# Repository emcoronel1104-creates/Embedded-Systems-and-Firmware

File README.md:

# Embedded-Systems-and-Firmware
Microcontroller projects, bare-metal firmware developments, and sensor interfacing protocols (C/C++).

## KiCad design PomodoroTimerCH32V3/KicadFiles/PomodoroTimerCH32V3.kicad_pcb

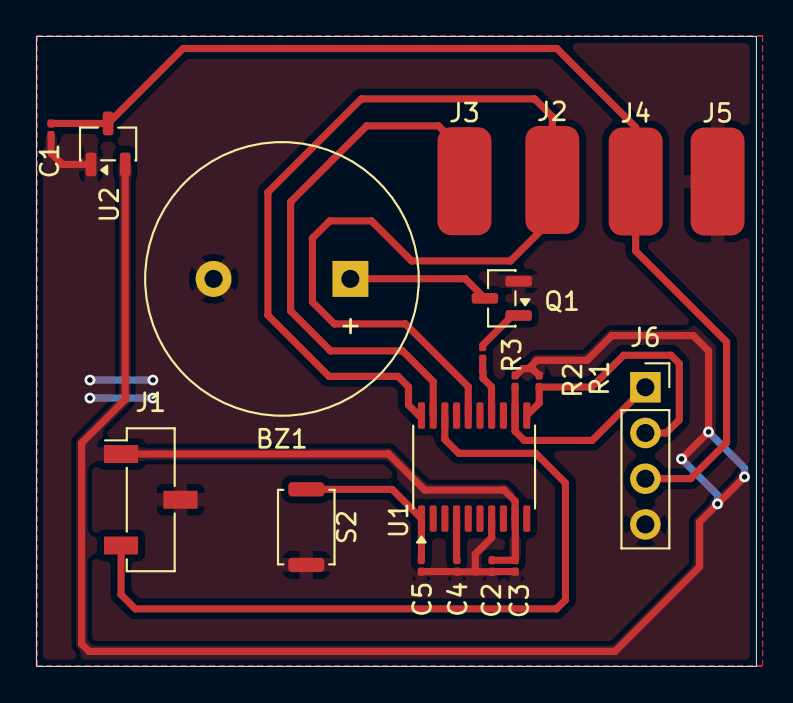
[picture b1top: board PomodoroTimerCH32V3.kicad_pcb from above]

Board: 2 copper layers, 40.0 x 35.0 mm, 19 parts (0 on the bottom side), 13 nets.

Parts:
BZ1: Buzzer; Buzzer_15x7.5RM7.6
C1, C2: 4.7uF; C_0201_0603Metric
C3, C4: 100uF; C_0201_0603Metric
C5: 0.1uF; C_0201_0603Metric
J1: Conn_01x03_Socket; PinSocket_1x03_P2.54mm_Vertical_SMD_Pin1Left
J2, J3, J4, J5: Conn_01x01_Pin; SolderWirePad_1x01_SMD_3x6mm
J6: Conn_01x02_Socket; PinSocket_1x04_P2.54mm_Vertical
Q1: BSS138; SOT-23
R1, R2, R3: 10k; R_0201_0603Metric
S2: SW_Push; SW_Push_SPST_NO_Alps_SKRK
U1: CH32V003FxPx; TSSOP-20_4.4x6.5mm_P0.65mm
U2: XC6206PxxxMR; SOT-23-3

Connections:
+3.3V: C2.1, C3.1, J1.1, R1.2, R2.2, U1.9 (VDD), U2.2 (VO)
+5V: C1.1, J4.1 (Pin_1_1), J6.3 (VCC), U2.3 (VI)
BUZZ: R3.1, U1.14 (PC4)
Button1: C5.1, S2.1, U1.1 (PD4)
GND: BZ1.2 (-), C1.2, C2.2, C3.2, C4.2, C5.2, J1.2, J5.1 (Pin_1_1), J6.4 (GND), Q1.2 (S), S2.2, U1.7 (VSS), U2.1 (GND)
NRST: C4.1, U1.4 (PD7)
unnamed: BZ1.1 (+), Q1.3 (D)
unnamed: Q1.1 (G), R3.2
PDIO: J1.3, U1.18 (PD1)
SCL: J6.1 (SCL), R2.1, U1.12 (PC2)
SDA: J6.2 (SDA), R1.1, U1.11 (PC1)
Touch1: J2.1 (Pin_1_1), U1.16 (PC6), U1.20 (PD3)
Touch2: J3.1 (Pin_1_1), U1.17 (PC7), U1.19 (PD2)

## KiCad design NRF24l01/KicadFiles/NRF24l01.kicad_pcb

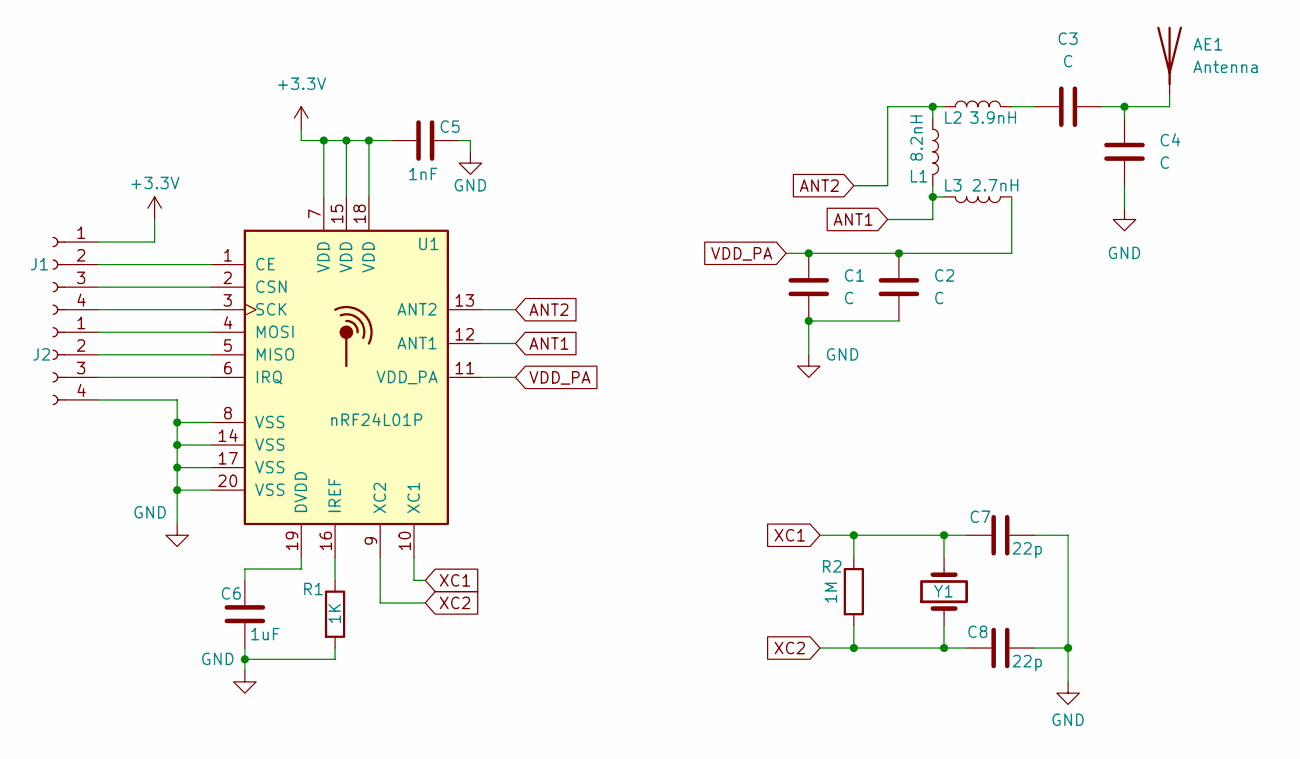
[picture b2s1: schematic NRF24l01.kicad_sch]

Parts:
AE1: Antenna; TestPoint_Pad_1.0x1.0mm
C1, C2, C3, C4: C; C_0402_1005Metric_Pad0.74x0.62mm_HandSolder
C5: 1nF; C_0402_1005Metric_Pad0.74x0.62mm_HandSolder
C6: 1uF; C_0402_1005Metric_Pad0.74x0.62mm_HandSolder
C7, C8: 22p; C_0402_1005Metric_Pad0.74x0.62mm_HandSolder
J1, J2: Conn_01x04_Socket; PinSocket_1x04_P2.54mm_Vertical_SMD_Pin1Left
L1: 8.2nH; L_0402_1005Metric_Pad0.77x0.64mm_HandSolder
L2: 3.9nH; L_0402_1005Metric_Pad0.77x0.64mm_HandSolder
L3: 2.7nH; L_0402_1005Metric_Pad0.77x0.64mm_HandSolder
R1: 1K; R_0402_1005Metric_Pad0.72x0.64mm_HandSolder
R2: 1M; R_0402_1005Metric_Pad0.72x0.64mm_HandSolder
U1: nRF24L01P; QFN-20-1EP_4x4mm_P0.5mm_EP2.5x2.5mm
Y1: Crystal; Crystal_SMD_HC49-SD_HandSoldering

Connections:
+3.3V: C5.1, J1.1, U1.7 (VDD), U1.15 (VDD), U1.18 (VDD)
ANT1: L1.2, L3.2, U1.12 (ANT1)
ANT2: L1.1, L2.1, U1.13 (ANT2)
GND: C1.2, C2.2, C4.1, C5.2, C6.1, C7.2, C8.2, J2.4, R1.2, U1.8 (VSS), U1.14 (VSS), U1.17 (VSS), U1.20 (VSS)
unnamed: AE1.1 (A_1), C3.2, C4.2
unnamed: C3.1, L2.2
unnamed: J1.2, U1.1 (CE)
unnamed: J1.3, U1.2 (CSN)
unnamed: J1.4, U1.3 (SCK)
unnamed: J2.1, U1.4 (MOSI)
unnamed: J2.2, U1.5 (MISO)
unnamed: J2.3, U1.6 (IRQ)
unnamed: C6.2, U1.19 (DVDD)
unnamed: R1.1, U1.16 (IREF)
VDD_PA: C1.1, C2.1, L3.1, U1.11 (VDD_PA)
XC1: C7.1, R2.1, U1.10 (XC1), Y1.2
XC2: C8.1, R2.2, U1.9 (XC2), Y1.1

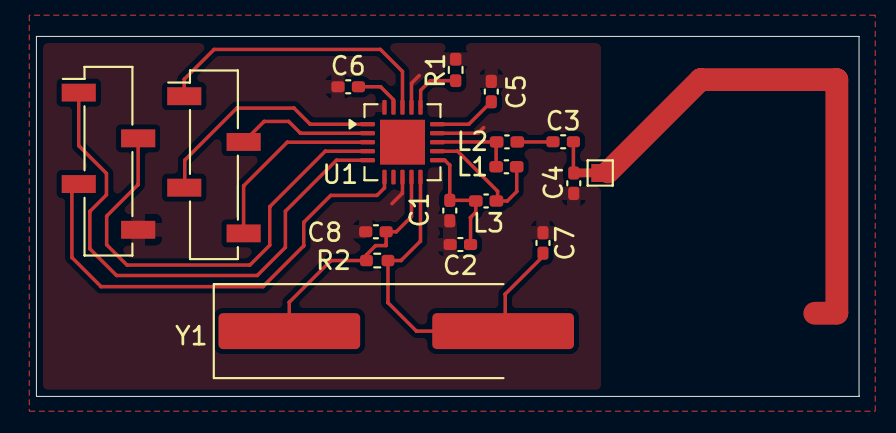
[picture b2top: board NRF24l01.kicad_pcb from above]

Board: 2 copper layers, 45.7 x 20.0 mm, 18 parts (0 on the bottom side), 17 nets.

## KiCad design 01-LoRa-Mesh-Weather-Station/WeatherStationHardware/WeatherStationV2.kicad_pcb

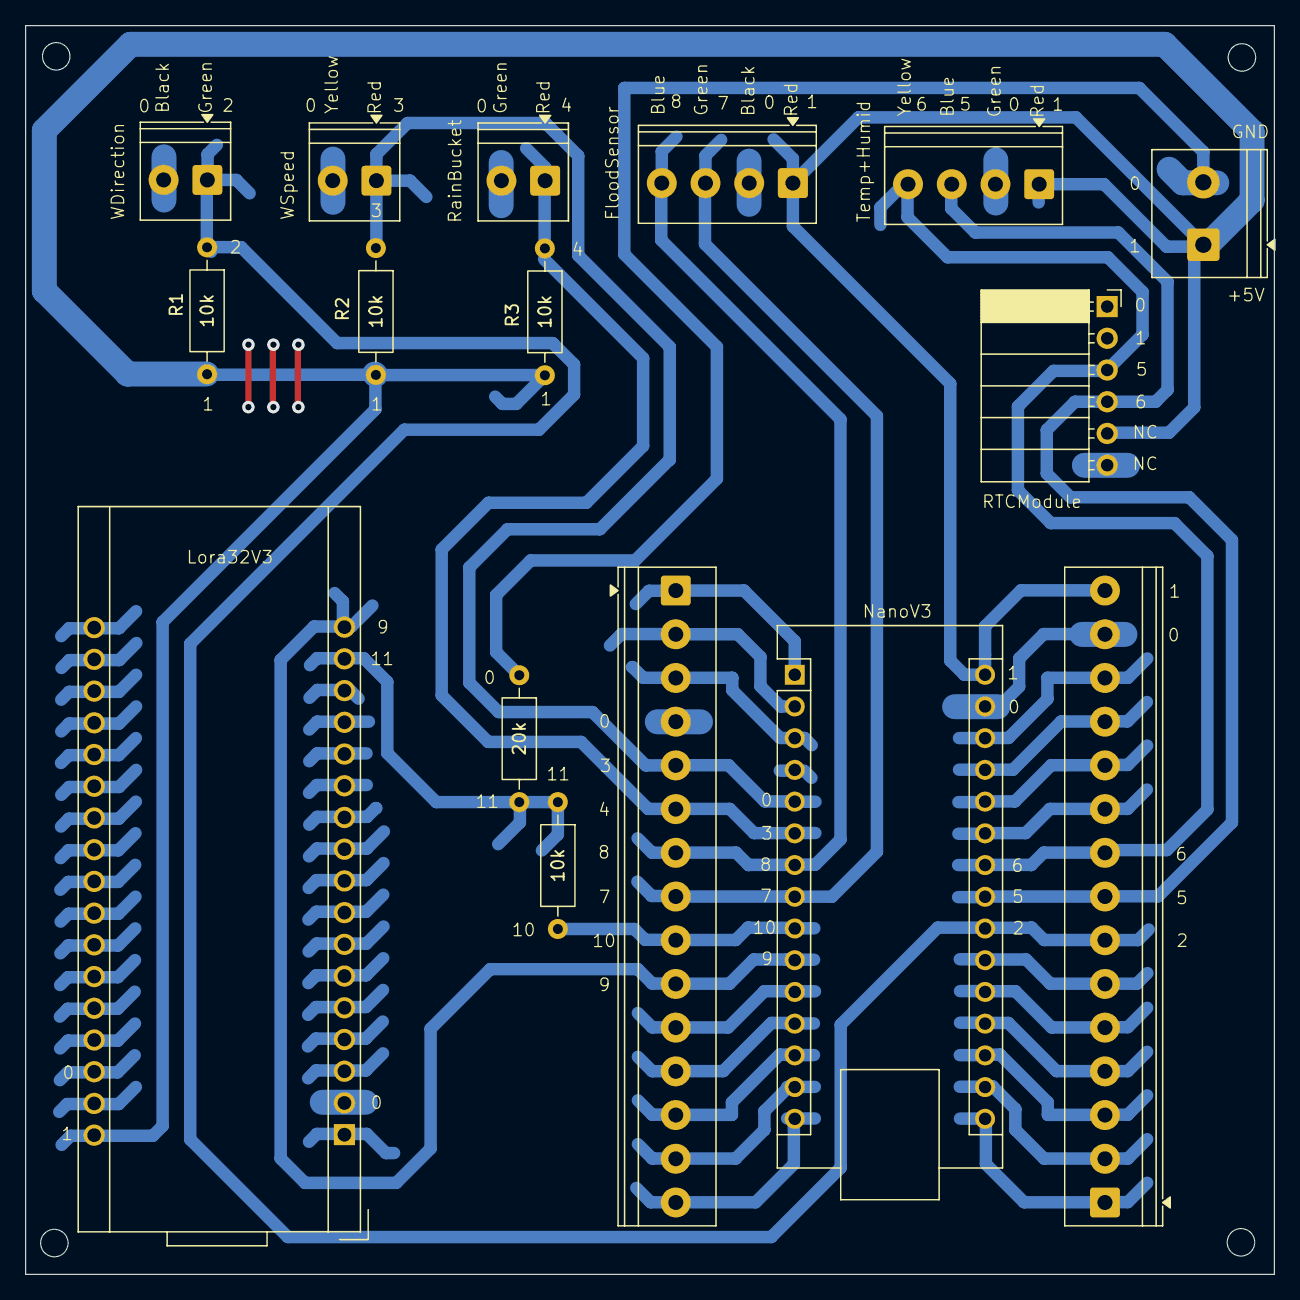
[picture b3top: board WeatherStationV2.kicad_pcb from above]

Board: 2 copper layers, 100.0 x 100.0 mm, 16 parts (0 on the bottom side), 30 nets.

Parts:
A1: NanoV3; Arduino_Nano
A2: Electrosmith_Daisy_Seed
J1, J2: Screw_Terminal_01x15; TerminalBlock_Phoenix_PT-1,5-15-3.5-H_1x15_P3.50mm_Horizont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
P4: Screw_Terminal_01x02; TerminalBlock_Phoenix_PT-1,5-2-5.0-H_1x02_P5.00mm_Horizontal
R1, R2, R3, R4: 10k; R_Axial_DIN0207_L6.3mm_D2.5mm_P10.16mm_Horizontal
R5: 20k; R_Axial_DIN0207_L6.3mm_D2.5mm_P10.16mm_Horizontal
S1, S2, S3: TerminalBlock_Phoenix_PT-1,5-2-3.5-H_1x02_P3.50mm_Horizontal
S4, S5: TerminalBlock_Phoenix_PT-1,5-4-3.5-H_1x04_P3.50mm_Horizontal
S6: PinSocket_1x06_P2.54mm_Horizontal

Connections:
+5V: A1.30 (VIN), A2.18 (5V), J1.30 (Pin_1), P4.1, R1.2, R2.2, R3.2, S4.1 (5V(Red)), S5.1 (5V), S6.1 (VCC)
A3: A1.22 (A3), J1.22 (Pin_9), R1.1, S1.1 (VCC(G))
D2: A1.5 (D2), J2.5 (Pin_11), R2.1, S2.1 (VCC(R))
D3: A1.6 (D3), J2.6 (Pin_10), R3.1, S3.1 (VCC)
Ground: A1.4 (GND), A1.29 (GND), A2.2 (GND), A2.20 (GND), J1.29 (Pin_2), J2.4 (Pin_12), P4.2, R5.1, S1.2 (GND(B)), S2.2 (GND(Y)), S3.2 (GND), S4.2 (GND(Grn)), S5.2 (GND), S6.2 (GND)
unnamed: A1.17 (3V3), J1.17 (Pin_14)
unnamed: A1.27 (+5V), J1.27 (Pin_4)
unnamed: A1.19 (A0), J1.19 (Pin_12)
unnamed: A1.20 (A1), J1.20 (Pin_11)
unnamed: A1.21 (A2), J1.21 (Pin_10)
unnamed: A1.25 (A6), J1.25 (Pin_6)
unnamed: A1.26 (A7), J1.26 (Pin_5)
unnamed: A1.18 (AREF), J1.18 (Pin_13)
unnamed: A1.1 (D0/TX), J2.1 (Pin_15)
unnamed: A1.2 (D1/RX), J2.2 (Pin_14)
unnamed: A1.11 (D8), J2.11 (Pin_5)
unnamed: A1.12 (D9), J2.12 (Pin_4)
unnamed: A1.13 (D10), J2.13 (Pin_3)
unnamed: A1.14 (D11), J2.14 (Pin_2)
unnamed: A1.15 (D12), J2.15 (Pin_1)
unnamed: A1.16 (D13), J1.16 (Pin_15)
unnamed: A2.16 (45), R4.1, R5.2
unnamed: A1.28 (~RESET), J1.28 (Pin_3)
unnamed: A1.3 (~RESET), J2.3 (Pin_13)
RX1: A1.8 (D5), J2.8, S5.3 (RX(Grn))
RX2: A1.10 (D7), A2.17 (46), J2.10 (Pin_6)
SCL(Ylw): A1.24 (A5), J1.24 (21), S4.4 (SCL(Ylw)), S6.4 (SCL(Ylw))
SDA(Blu): A1.23 (A4), J1.23 (Pin_8), S4.3 (SDA(Blu)), S6.3 (SDA(Blu))
TX1: A1.7 (D4), J2.7 (Pin_9), S5.4 (TX(Blu))
TX2: A1.9 (D6), J2.9 (Pin_7), R4.2
